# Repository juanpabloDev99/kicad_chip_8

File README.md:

# kicad_chip_8
Chip 8 board emulator using kicad

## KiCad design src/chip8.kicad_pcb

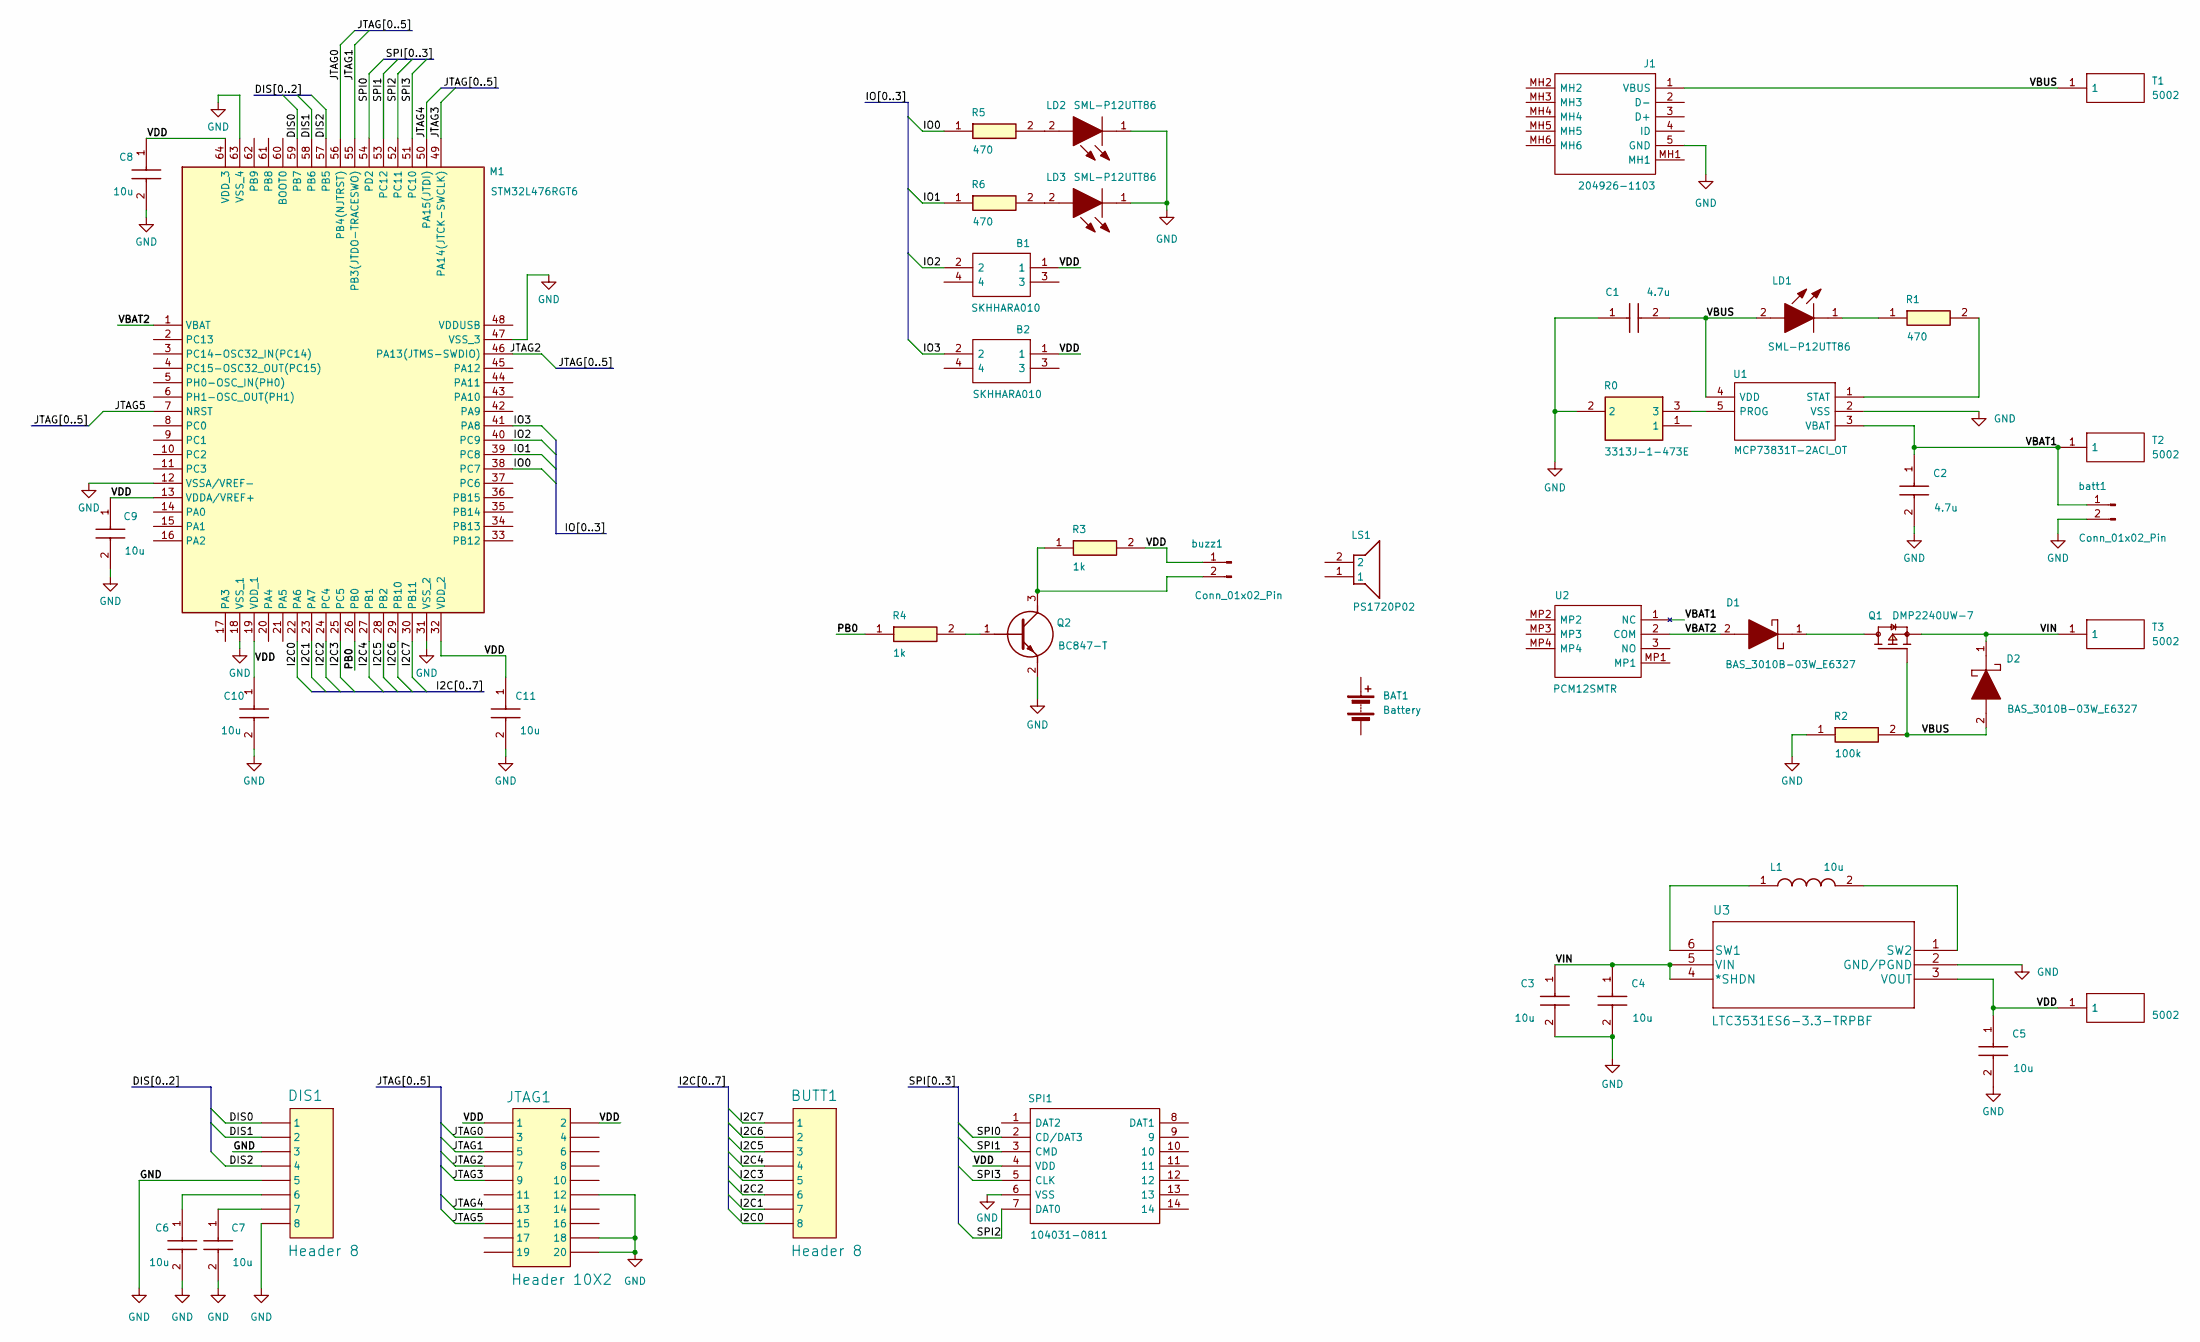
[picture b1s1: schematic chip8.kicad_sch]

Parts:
B1, B2: SKHHARA010; Mouser Part Number 688-SKHHAR
BAT1: Battery
BUTT1: Header 8; PinSocket_1x08_P2.54mm_Vertical
C1, C2: 4.7u; MAJx16; Mouser Part Number 963-MAJCT168BB7105KT
C3, C4, C5, C6, C7, C8, C9, C10, C11: 10u; MAJx16; Mouser Part Number 963-MAJCT168BB7105KT
D1, D2: BAS_3010B-03W_E6327; SOD2513X110N; Mouser Part Number 726-BAS3010B03WE6327
DIS1: Header 8; PinSocket_1x08_P2.54mm_Vertical
J1: 204926-1103; 2049261103; Mouser Part Number 538-204926-1103
JTAG1: Header 10X2; PinSocket_2x10_P2.54mm_Vertical
L1: 10u; INDPM132129X350N; Mouser Part Number 70-IHLP5050CEER100M1
LD1, LD2, LD3: SML-P12UTT86; LEDC1006X25N; Mouser Part Number 755-SML-P12UTT86
LS1: PS1720P02; PS17_1; Mouser Part Number 810-PS1720P02
M1: STM32L476RGT6; QFP50P1200X1200X160-64N; Mouser Part Number 511-STM32L476RGT6
Q1: DMP2240UW-7; SOT65P210X110-3N; PARTREV 6-3
Q2: BC847-T; SOT95P240X115-3N; Mouser Part Number 583-BC847
R0: 3313J-1-473E; 3313J-1; Mouser Part Number 652-3313J-1-473E
R1, R5, R6: 470; ERA8KEB1004V; Mouser Part Number 667-ERA-8VRB1002V
R2: 100k; ERA8KEB1004V; Mouser Part Number 667-ERA-8VRB1002V
R3, R4: 1k; ERA8KEB1004V; Mouser Part Number 667-ERA-8VRB1002V
SPI1: 104031-0811; 1040310811; Mouser Part Number 538-104031-0811
T1, T2, T3, T4: 5002; Mouser Part Number 534-5002
U1: MCP73831T-2ACI_OT; SOT95P270X145-5N; Mouser Part Number 579-MCP73831T-2ACIOT
U2: PCM12SMTR; Mouser Part Number 611-PCM12SMTR
U3: LTC3531ES6-3.3-TRPBF; TSOT-23_S6
batt1: Conn_01x02_Pin; PinSocket_1x02_P2.54mm_Vertical
buzz1: Conn_01x02_Pin; PinSocket_1x02_P2.54mm_Vertical

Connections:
/DIS0: DIS1.1, M1.59 (PB7)
/DIS1: DIS1.2, M1.58 (PB6)
/DIS2: DIS1.4, M1.57 (PB5)
/I2C0: BUTT1.8, M1.22 (PA6)
/I2C1: BUTT1.7, M1.23 (PA7)
/I2C2: BUTT1.6, M1.24 (PC4)
/I2C3: BUTT1.5, M1.25 (PC5)
/I2C4: BUTT1.4, M1.27 (PB1)
/I2C5: BUTT1.3, M1.28 (PB2)
/I2C6: BUTT1.2, M1.29 (PB10)
/I2C7: BUTT1.1, M1.30 (PB11)
/IO0: M1.38 (PC7), R5.1
/IO1: M1.39 (PC8), R6.1
/IO2: B1.2, M1.40 (PC9)
/IO3: B2.2, M1.41 (PA8)
/JTAG0: JTAG1.3, M1.56 (PB4(NJTRST))
/JTAG1: JTAG1.5, M1.55 (PB3(JTDO-TRACESWO))
/JTAG2: JTAG1.7, M1.46 (PA13(JTMS-SWDIO))
/JTAG3: JTAG1.9, M1.49 (PA14(JTCK-SWCLK))
/JTAG4: JTAG1.13, M1.50 (PA15(JTDI))
/JTAG5: JTAG1.15, M1.7 (NRST)
/PB0: M1.26 (PB0), R4.1
/SPI0: M1.54 (PD2), SPI1.2 (CD/DAT3)
/SPI1: M1.53 (PC12), SPI1.3 (CMD)
/SPI2: M1.52 (PC11), SPI1.7 (DAT0)
/SPI3: M1.51 (PC10), SPI1.5 (CLK)
/VBAT1: C2.1, T2.1, U1.3 (VBAT), U2.1 (NC), batt1.1
/VBAT2: D1.2, M1.1 (VBAT), U2.2 (COM)
/VBUS: C1.2, D2.2, J1.1 (VBUS), LD1.2, Q1.1, R2.2, T1.1, U1.4 (VDD)
/VDD: B1.1, B2.1, C5.1, C8.1, C9.1, C10.1, C11.1, JTAG1.1, JTAG1.2, M1.13 (VDDA/VREF+), M1.19 (VDD_1), M1.32 (VDD_2), M1.64 (VDD_3), R3.2, SPI1.4 (VDD), T4.1, U3.3 (VOUT), buzz1.1
/VIN: C3.1, C4.1, D2.1, Q1.2, T3.1, U3.4 (*SHDN), U3.5 (VIN)
GND: C1.1, C2.2, C3.2, C4.2, C5.2, C6.2, C7.2, C8.2, C9.2, C10.2, C11.2, DIS1.3, DIS1.5, DIS1.8, J1.5 (GND), JTAG1.12, JTAG1.18, JTAG1.20, LD2.1, LD3.1, M1.12 (VSSA/VREF-), M1.18 (VSS_1), M1.31 (VSS_2), M1.47 (VSS_3), M1.63 (VSS_4), Q2.2 (E), R0.2, R2.1, SPI1.6 (VSS), U1.2 (VSS), U3.2 (GND/PGND), batt1.2
unnamed: C6.1, DIS1.6
unnamed: C7.1, DIS1.7
unnamed: D1.1, Q1.3
unnamed: LD1.1, R1.1
unnamed: LD2.2, R5.2
unnamed: LD3.2, R6.2
unnamed: Q2.1 (B), R4.2
unnamed: Q2.3 (C), R3.1, buzz1.2
unnamed: R0.3, U1.5 (PROG)
unnamed: R1.2, U1.1 (STAT)
unnamed: L1.1, U3.6 (SW1)
unnamed: L1.2, U3.1 (SW2)

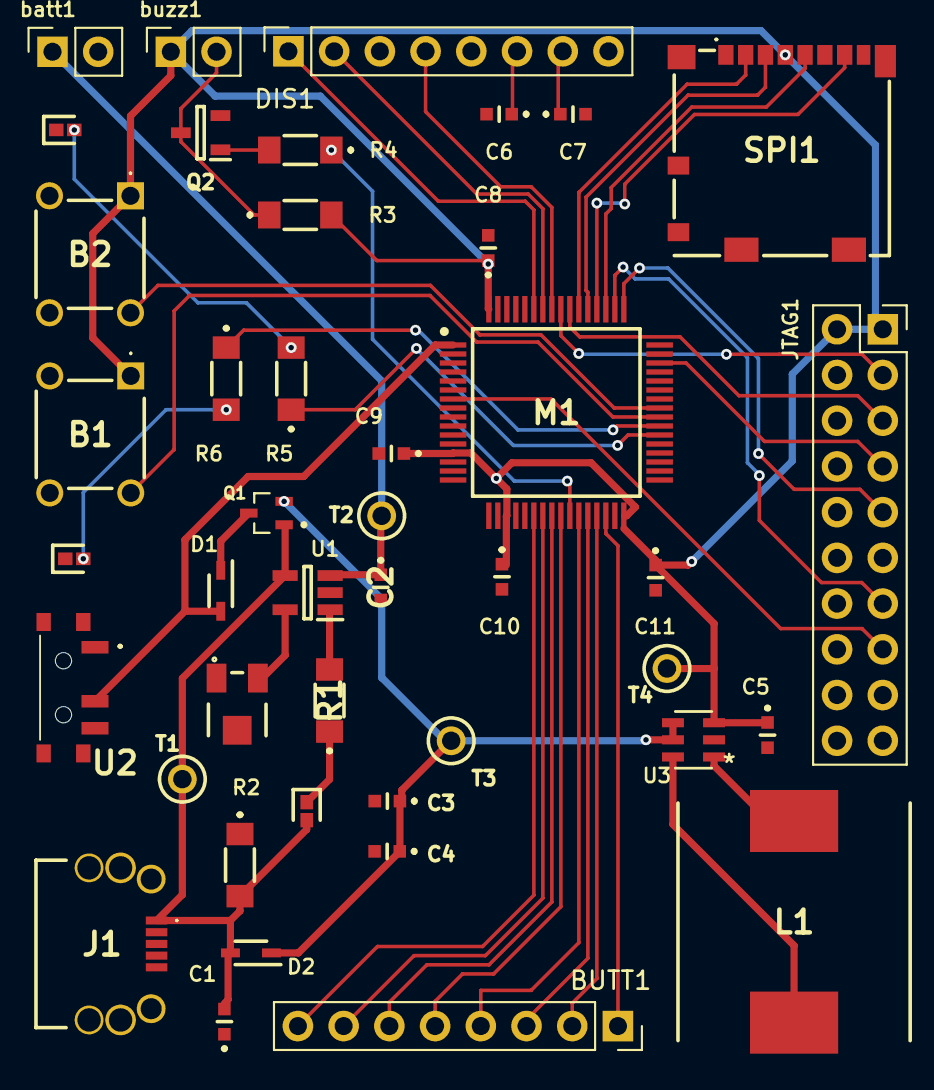
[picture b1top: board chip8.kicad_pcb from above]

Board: 2 copper layers, 43 parts (0 on the bottom side), 44 nets.

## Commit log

2025-03-25 second commit
2025-03-30 ground plane and corrections done
